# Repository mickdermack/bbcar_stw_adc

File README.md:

# bbcar_stw_adc

ESP32 and STM32 board for steering wheel mounted operation on a Bobby Car by mickdermack and fanosta.

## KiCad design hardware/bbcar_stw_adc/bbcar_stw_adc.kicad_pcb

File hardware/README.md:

# Prerequisites

Add the following footprint library under the name "otter": https://github.com/Jan--Henrik/KiCAD-libs

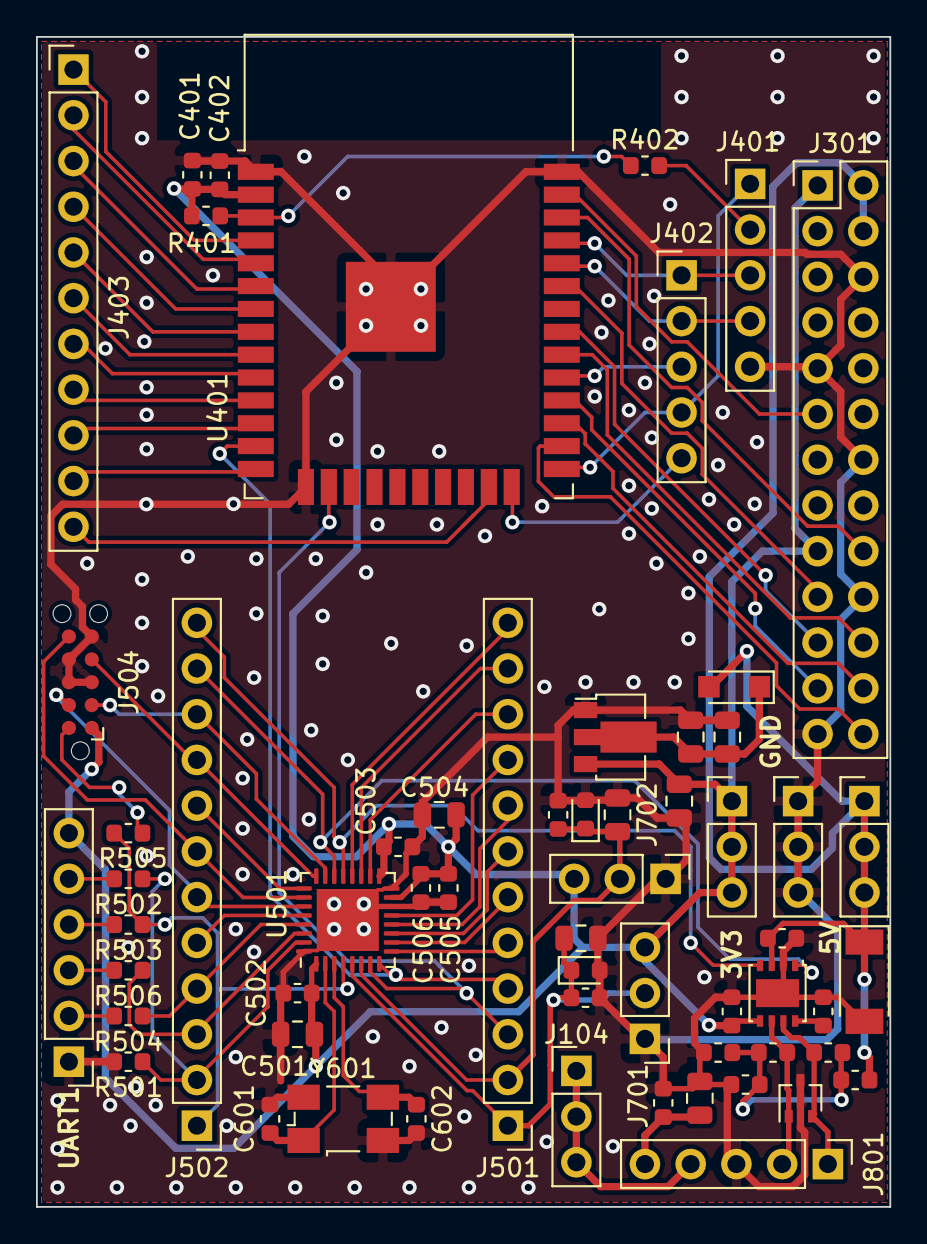
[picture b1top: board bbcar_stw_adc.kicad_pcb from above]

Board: 2 copper layers, 47.4 x 65.0 mm, 60 parts (0 on the bottom side), 67 nets.

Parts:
C201, C501: 4.7u; C_0805_2012Metric
C202, C203, C504, C701, C702: 1u; C_0805_2012Metric
C401, C502, C503, C505, C801, C802, C803: 0.1u; C_0603_1608Metric
C402: 10u; C_0603_1608Metric
C506: 10n; C_0603_1608Metric
C601, C602: 18p; C_0603_1608Metric
C804: 4.7n; C_0805_2012Metric
D101: 5V; D_SOD-128
D201: D_Schottky; D_SOD-123W
D701, D702: 3.3V; D_0603_1608Metric
D801: ESDCAN05-2BWY; SOT-323_SC-70
J101, J102, J103, J104, J701, J702: Conn_01x03; PinHeader_1x03_P2.54mm_Vertical
J301: Conn_02x13_Odd_Even; PinHeader_2x13_P2.54mm_Vertical
J401, J402, J801: Conn_01x05; PinHeader_1x05_P2.54mm_Vertical
J403: Conn_01x11; PinHeader_1x11_P2.54mm_Vertical
J501, J502: Conn_01x12; PinHeader_1x12_P2.54mm_Vertical
J503: Conn_01x06; PinHeader_1x06_P2.54mm_Vertical
J504: Tag-Connect_2050; Tag-Connect_TC2050-IDC-NL_2x05_P1.27mm_Vertical
R401, R501, R801, R802, R803: 10k; R_0603_1608Metric
R402, R502, R503, R504, R505, R506: 1k; R_0603_1608Metric
R701, R702: 47k; R_0603_1608Metric
R804, R805: 60.4R; R_0603_1608Metric
R806: 1M; R_0603_1608Metric
U201: MCP1703A-3302_SOT89; SOT-89-3
U401: ESP32-WROOM-32
U501: STM32G431KBUx; QFN-32-1EP_5x5mm_P0.5mm_EP3.45x3.45mm
U801: MCP2542FDxMF; DFN-8-1EP_3x3mm_P0.65mm_EP1.55x2.4mm
Y601: Crystal_GND24; Crystal_SMD_Abracon_ABMM2-4Pin_6.0x3.6mm

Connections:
+3V3: C203.1, C401.1, C402.1, C501.1, C502.1, C503.1, C504.1, C505.1, C506.1, C801.1, J101.1, J101.2, J101.3, J301.1, J301.17, J503.6, J504.1, J701.3, J702.3, R401.1, U201.3, U401.2, U501.1, U501.15, U501.17, U801.5
+5V: C802.1, D101.1, D201.2, J103.1, J103.2, J103.3, J301.2, J301.4, R802.1, U801.3
/CAN/CAN_H: D801.2, J801.1, R804.1, U801.7
/CAN/CAN_L: D801.1, J801.2, R805.2, U801.6
/CAN/CAN_RX: J502.12, U501.21, U801.4
/CAN/CAN_TX: J502.11, U501.22, U801.1
/Display_Conn/COPI: J301.19, U401.33
/ESP32/EN: R401.2, R402.1, U401.3
/ESP32/IO4: J301.26, U401.26
/ESP32/IO13: J501.3, U401.16, U501.7
/ESP32/IO14: J501.4, U401.13, U501.8
/ESP32/IO16: J301.24, U401.27
/ESP32/IO17: J301.23, U401.28
/ESP32/IO18: J301.22, U401.30
/ESP32/IO19: J301.21, U401.31
/ESP32/IO22: J301.18, U401.36
/ESP32/IO23: J301.11, U401.37
/ESP32/IO36: J403.1, U401.4
/ESP32/IO39: J403.2, U401.5
/STM32/BOOT0: J502.2, R501.1, R502.1, U501.31
/STM32/HSE_Crystal/XTAL1: C601.1, U501.2, Y601.1
/STM32/HSE_Crystal/XTAL2: C602.1, U501.3, Y601.3
/STM32/PA0: C701.1, D701.1, J501.1, J701.2, R701.1, U501.5
/STM32/PA1: C702.1, D702.1, J501.2, J702.2, R702.1, U501.6
/STM32/PB0: J501.9, U501.13
/STM32/PB5: J502.5, U501.28
/STM32/SWCLK: J502.9, J504.4, U501.24
/STM32/SWDIO: J502.10, J504.2, U501.23
/STM32/SWO: J502.7, J504.6, U501.26
/STM32/UART1_RXD: J502.3, R506.1, U501.30
/STM32/UART1_TXD: J502.4, R504.1, U501.29
/STM32/~RESET: J502.1, R503.1, R505.1, U501.4
/STM32/~TRST: J502.6, J504.9, U501.27
GND: C201.2, C202.2, C203.2, C401.2, C402.2, C501.2, C502.2, C503.2, C504.2, C505.2, C506.2, C601.2, C602.2, C701.2, C702.2, C801.2, C802.2, C803.2, C804.2, D101.2, D701.2, D702.2, D801.3, J102.1, J102.2, J102.3, J301.6, J301.9, J301.14, J301.20, J301.25, J401.5, J503.1, J504.3, J504.5, J504.7, J504.8, J701.1, J702.1, J801.3, R501.2, R701.2, R702.2, R801.2, R803.2, R806.2, U201.1, U401.1, U401.15, U401.38, U401.39, U501.14, U501.16, U501.32, U501.33, U801.2, U801.9, Y601.2, Y601.4
unnamed: C201.1, C202.1, D201.1, U201.2
unnamed: C803.1, R802.2, R803.1, R804.2, R805.1
unnamed: C804.1, J801.5, R806.1
unnamed: J401.1, J402.4, U401.25
unnamed: J401.2, R402.2
unnamed: J401.3, J402.1, U401.35
unnamed: J401.4, J402.2, U401.34
unnamed: J402.3, U401.29
unnamed: J402.5, U401.24
unnamed: J403.3, U401.6
unnamed: J403.4, U401.7
unnamed: J403.5, U401.8
unnamed: J403.6, U401.9
unnamed: J403.7, U401.10
unnamed: J403.8, U401.11
unnamed: J403.9, U401.12
unnamed: J403.10, U401.14
unnamed: J403.11, U401.23
unnamed: J501.5, U501.9
unnamed: J501.6, U501.10
unnamed: J501.7, U501.11
unnamed: J501.8, U501.12
unnamed: J501.10, U501.18
unnamed: J501.11, U501.19
unnamed: J501.12, U501.20
unnamed: J502.8, U501.25
unnamed: J503.2, R504.2
unnamed: J503.3, R506.2
unnamed: J503.4, R503.2
unnamed: J503.5, R502.2
unnamed: J504.10, R505.2
unnamed: R801.1, U801.8
VBUS: J104.1, J104.2, J104.3, J801.4
